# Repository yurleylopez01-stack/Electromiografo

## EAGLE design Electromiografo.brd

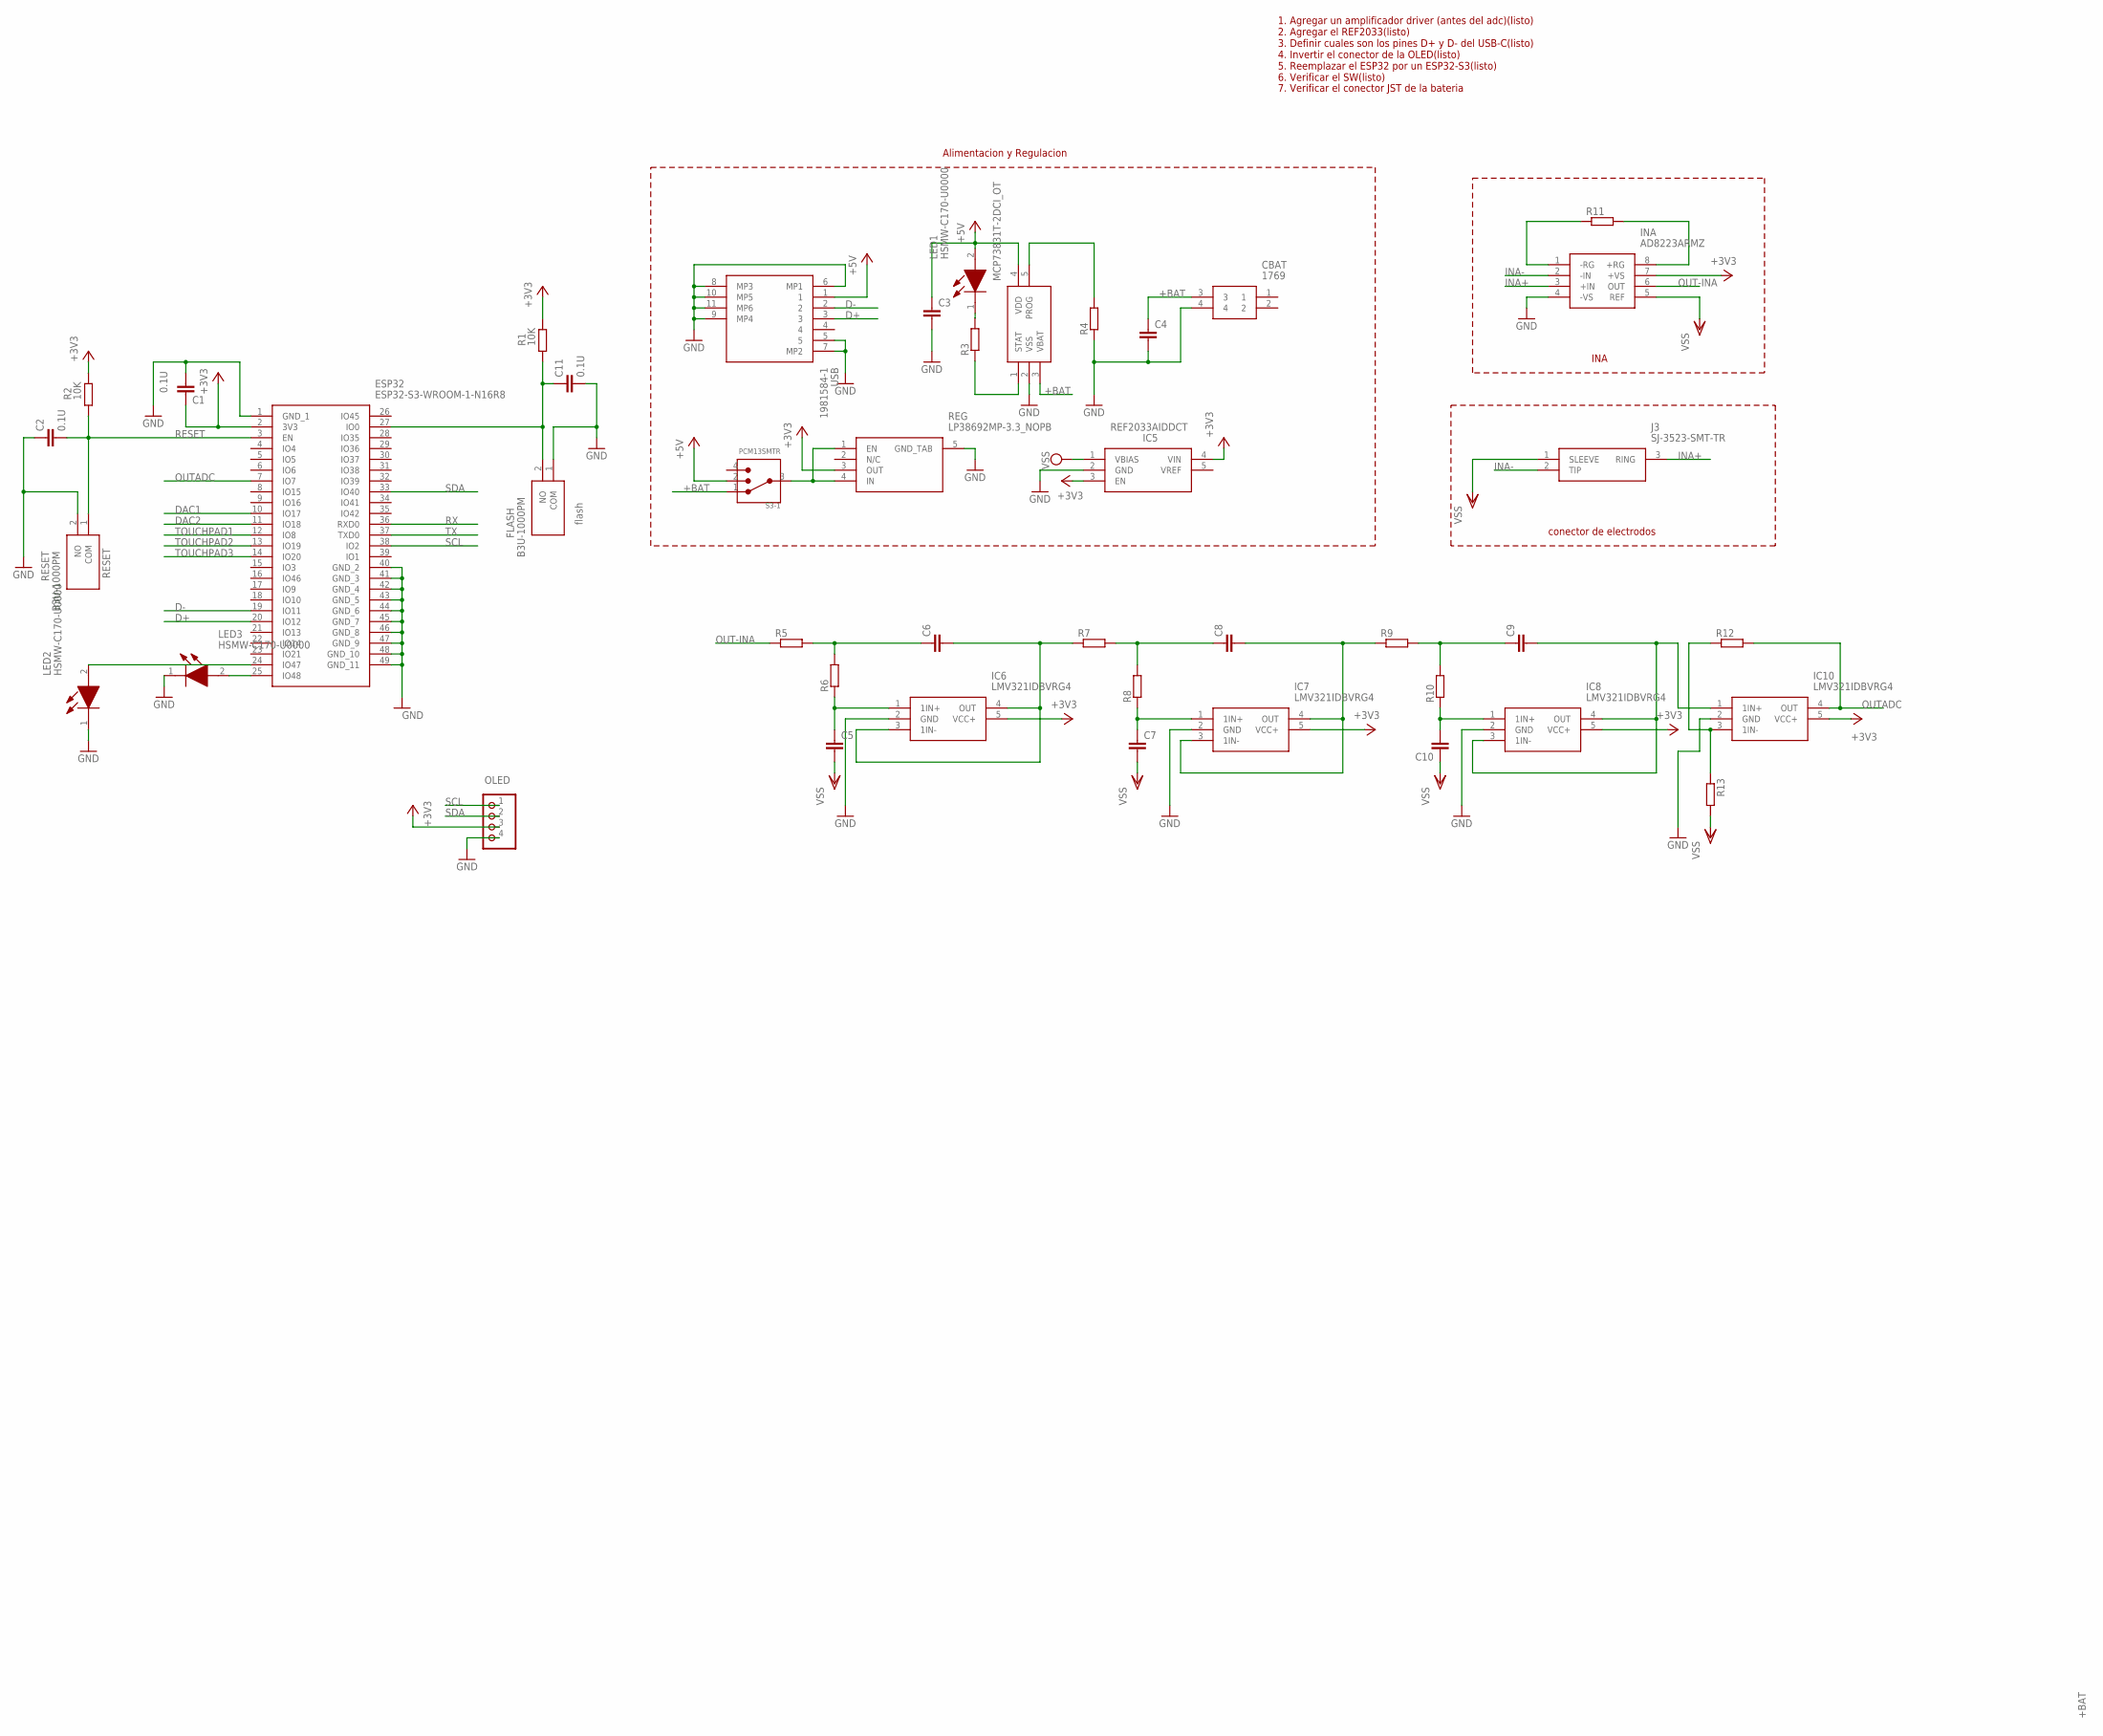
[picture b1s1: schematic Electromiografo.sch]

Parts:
C1, C2, C11: 0.1U; C0603
C3, C4, C5, C6, C7, C8, C9, C10: C-EUC0805; C0805
CBAT: 1769
ESP32: ESP32-S3-WROOM-1-N16R8; ESP32S3WROOM1N16R8
FLASH: B3U-1000PM; B3U1000PM
IC2: MCP73831T-2DCI_OT; SOT95P270X145-5N
IC5: REF2033AIDDCT; SOT95P280X110-5N
IC6, IC7, IC8, IC10: LMV321IDBVRG4; SOT95P280X145-5N
INA: AD8223ARMZ; SOP65P490X110-8N@1
J3: SJ-3523-SMT-TR; SJ3523SMTTR
JP1: PINHD-1X4/90; 1X04/90
LED1, LED2, LED3: HSMW-C170-U0000; LEDC2012X90N
R1, R2: 10K; R0805
R3, R4, R5, R6, R7, R8, R9, R10, R11, R12, R13: R-EU_R0805; R0805
REG: LP38692MP-3.3_NOPB; SOT150P700X180-5N
RESET: B3U-1000PM; B3U1000PM
S3-1: PCM13SMTR; SW_PCM13SMTR
USB: 1981584-1; 19815841

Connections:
+3V3: C1.2, ESP32.2 (3V3), IC5.4 (VIN), IC6.5 (VCC+), IC7.5 (VCC+), IC8.5 (VCC+), IC10.5 (VCC+), INA.7 (+VS), JP1.3, R1.2, R2.2, REG.3 (OUT)
+5V: C3.1, IC2.4 (VDD), LED1.2 (A), S3-1.2, USB.1
+BAT: C4.1, CBAT.3, IC2.3 (VBAT), S3-1.1
D+: ESP32.20 (IO12), USB.3
D-: ESP32.19 (IO11), USB.2
DAC1: ESP32.10 (IO17)
DAC2: ESP32.11 (IO18)
GND: C1.1, C2.1, C3.2, C4.2, C11.2, CBAT.4, ESP32.1 (GND_1), ESP32.40 (GND_2), ESP32.41 (GND_3), ESP32.42 (GND_4), ESP32.43 (GND_5), ESP32.44 (GND_6), ESP32.45 (GND_7), ESP32.46 (GND_8), ESP32.47 (GND_9), ESP32.48 (GND_10), ESP32.49 (GND_11), FLASH.1 (COM), IC2.2 (VSS), IC5.2 (GND), IC6.2 (GND), IC7.2 (GND), IC8.2 (GND), IC10.2 (GND), INA.4 (-VS), JP1.4, LED2.1 (K), LED3.1 (K), R4.1, REG.5 (GND_TAB), RESET.2 (NO), USB.5, USB.6 (MP1), USB.7 (MP2), USB.8 (MP3), USB.9 (MP4), USB.10 (MP5), USB.11 (MP6)
INA+: INA.3 (+IN), J3.3 (RING)
INA-: INA.2 (-IN), J3.2 (TIP)
unnamed: C11.1, ESP32.27 (IO0), FLASH.2 (NO), R1.1
unnamed: LED1.1 (K), R3.2
unnamed: ESP32.25 (IO48), LED3.2 (A)
unnamed: ESP32.24 (IO47), LED2.2 (A)
unnamed: IC10.3 (1IN-), R12.1, R13.1
unnamed: IC2.1 (STAT), R3.1
unnamed: IC2.5 (PROG), R4.2
unnamed: REG.1 (EN), REG.4 (IN), S3-1.3
unnamed: C6.2, IC6.3 (1IN-), IC6.4 (OUT), R7.1
unnamed: C6.1, R5.2, R6.2
unnamed: C5.1, IC6.1 (1IN+), R6.1
unnamed: C9.1, R9.2, R10.2
unnamed: C7.1, IC7.1 (1IN+), R8.1
unnamed: C8.1, R7.2, R8.2
unnamed: C8.2, IC7.3 (1IN-), IC7.4 (OUT), R9.1
unnamed: C10.2, IC8.1 (1IN+), R10.1
unnamed: C9.2, IC8.3 (1IN-), IC8.4 (OUT), IC10.1 (1IN+)
unnamed: INA.8 (+RG), R11.2
unnamed: INA.1 (-RG), R11.1
OUT-INA: INA.6 (OUT), R5.1
OUTADC: ESP32.7 (IO7), IC10.4 (OUT), R12.2
RESET: C2.2, ESP32.3 (EN), R2.1, RESET.1 (COM)
RX: ESP32.36 (RXD0)
SCL: ESP32.38 (IO2), JP1.1
SDA: ESP32.33 (IO40), JP1.2
TOUCHPAD1: ESP32.12 (IO8)
TOUCHPAD2: ESP32.13 (IO19)
TOUCHPAD3: ESP32.14 (IO20)
TX: ESP32.37 (TXD0)
VSS: C5.2, C7.2, C10.1, IC5.1 (VBIAS), INA.5 (REF), J3.1 (SLEEVE), R13.2

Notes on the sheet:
OLED
conector de electrodos
INA
Alimentacion y Regulacion
1. Agregar un amplificador driver (antes del adc)(listo) 2. Agregar el REF2033(listo) 3. Definir cuales son los pines D+ y D- del USB-C(listo) 4. Invertir el conector de la OLED(listo) 5. Reemplazar el ESP32 por un ESP32-S3(listo) 6. Verificar el SW(listo)
7. Verificar el conector JST de la bateria
flash
RESET

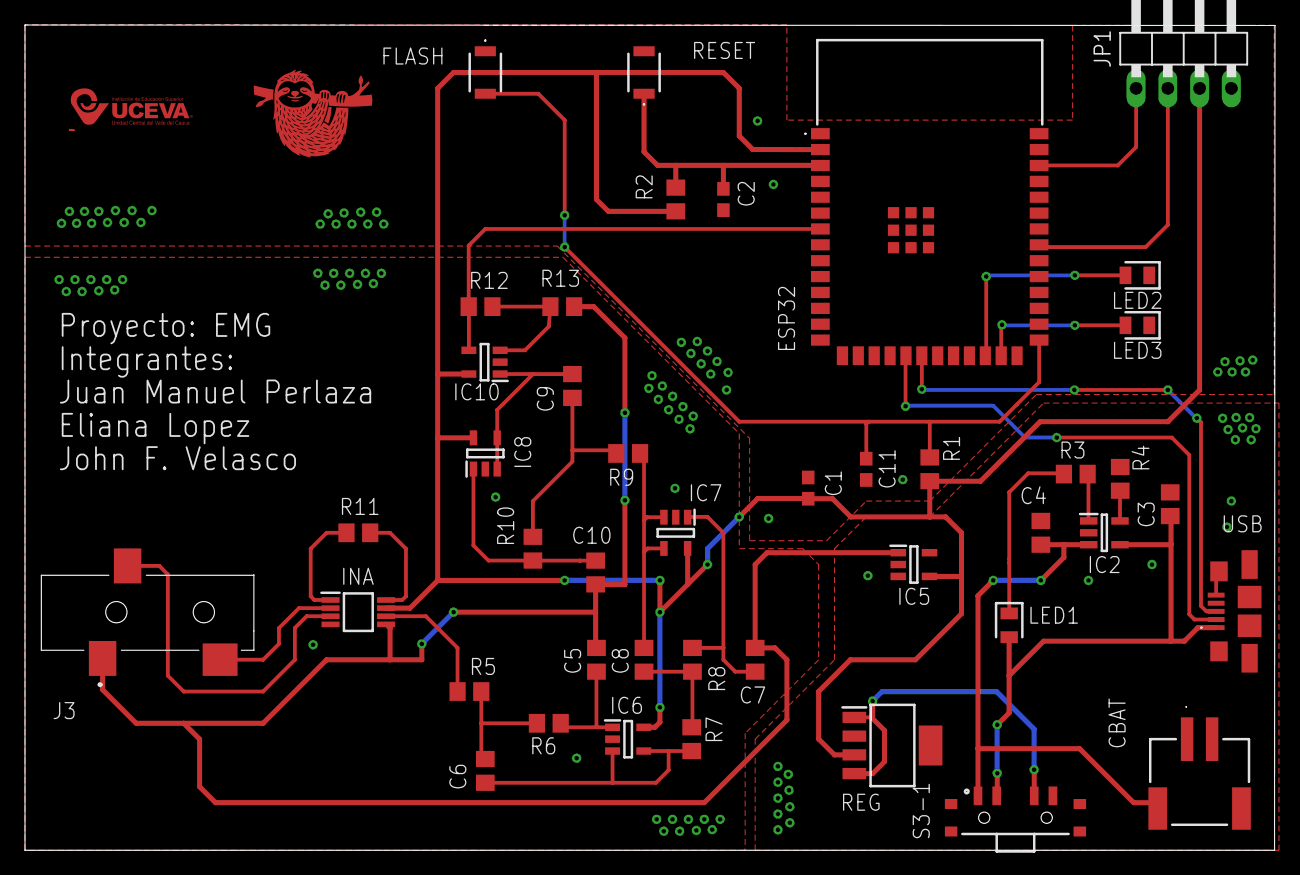
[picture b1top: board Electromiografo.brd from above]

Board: 2 copper layers, 100.0 x 66.0 mm, 43 parts (0 on the bottom side), 33 nets.

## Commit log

2025-10-05 Archivo de prueba
2025-10-05 Archivo prueba Juan
2025-10-05 archivo esquematico john
2025-10-05 Archivo esquematico Eliana - Agregue esquematico de alimentacion, regulacion y voltaje de referencia
2025-10-05 Archivo de Libreria
2025-10-05 Se agrego el esquematico del filtro pasa bajas y el INA
2025-10-05 Anado el preinforme del proyecto
2025-10-05 Archivo esquematico
2025-10-06 hojas de datos
2025-10-10 Se corrigieron algunos bloques y se anoto lo faltante
2025-10-10 Se corrigio el pin SDA
2025-10-11 Actualizacion pre informe, se añadio metodologia e introduccion
2025-10-13 Se añafio anexo de vision y mision
2025-10-13 modificaciones puntos 2,4,5,6
2025-10-17 modificaciones terminadas
2025-10-23 Se remplazo conector de bateria
2025-10-23 Se ubicaron los elementos en la pcb
2025-10-24 Se ruteo las pistas de INA, Filtro y conector de electrodos
2025-10-24 modificacion pulsadores
2025-10-24 Se rutearon las pistas de alimentacion del pcb
2025-10-24 Se termino version uno del pcb
2025-10-31 corregido el switche
2025-10-31 Modificaciones esquematico, version 2 de pcb
2025-11-03 nombres
2025-11-04 Se agrego logotipos a la pcb
2025-11-04 Se realozaron ajustes finales a la pcb
2025-11-05 fix: PCB reviewed
2025-11-05 Finalizacion de PCB
2025-11-25 Se agrego carpeta del codigo
2025-11-25 Se adjunto informe final del Electromiografo
